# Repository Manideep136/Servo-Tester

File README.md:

# Servo-Tester
# Servo Tester

A simple standalone circuit for testing hobby servo motors by generating an adjustable PWM signal, without needing a microcontroller.
https://github.com/Manideep136/Servo-Tester/blob/main/sero%20tester/SERVO/TOP.png

## Overview

This circuit generates a variable-width PWM pulse (typically ~50Hz, 1ms–2ms pulse width) to drive a standard hobby servo, letting you manually sweep it or center it using a potentiometer — useful for testing, calibrating, or centering servos before installing them in a project.

## Circuit Description

*(Adjust the table below to match your actual component values)*

| Component | Value | Function |
|---|---|---|
| U1 | NE555 / LM555 | Astable/monostable oscillator generating the PWM signal |
| R1 | ~10kΩ (fixed) | Timing resistor |
| RV1 | 10kΩ Potentiometer | Adjusts pulse width (servo position) |
| C1 | ~10nF–100nF | Timing capacitor (sets base pulse frequency) |
| C2 | 10µF | Power supply decoupling capacitor |
| J1 | 3-pin header (Signal, VCC, GND) | Servo output connector |
| J2 | Screw Terminal / DC Jack | Power input (typically 4.8V–6V) |

## Schematic

https://github.com/Manideep136/Servo-Tester/blob/main/sero%20tester/SERVO/schematic.png

## PCB Layout

https://github.com/Manideep136/Servo-Tester/blob/main/sero%20tester/SERVO/LAYOUT.png

## Files

- `*.kicad_pro`, `*.kicad_sch`, `*.kicad_pcb` — KiCad project, schematic, and PCB layout files
- `gerbers/` — Fabrication files (Gerber + drill files) ready to send to a PCB manufacturer
- `images/` — Renders and screenshots of the schematic, PCB, and 3D model

## How to Use

1. Open `Servo-Tester.kicad_pro` in KiCad to view or edit the schematic and PCB.
2. To manufacture the board, send the contents of `gerbers/` to your preferred PCB fab (e.g. JLCPCB, PCBWay).
3. Connect a servo to the 3-pin output header (matching Signal/VCC/GND orientation to your servo's connector).
4. Power the board with 4.8V–6V DC.
5. Turn the potentiometer to sweep the servo from one end to the other, or center it to find the servo's neutral position.

## Notes

- Double-check your servo's signal pin orientation before connecting — reversed polarity can damage the servo or the tester.
- If using a 555 timer in astable mode, verify your R/C values produce a ~50Hz signal with a 1ms–2ms high pulse range (standard servo PWM range) using an oscilloscope or logic analyzer if available.
- A small heatsink or careful current limiting isn't usually necessary for a single small servo, but avoid powering multiple/large servos directly from this board without a beefier supply.

## License

Feel free to specify a license here (e.g. MIT, CERN-OHL) if you'd like others to reuse this design.

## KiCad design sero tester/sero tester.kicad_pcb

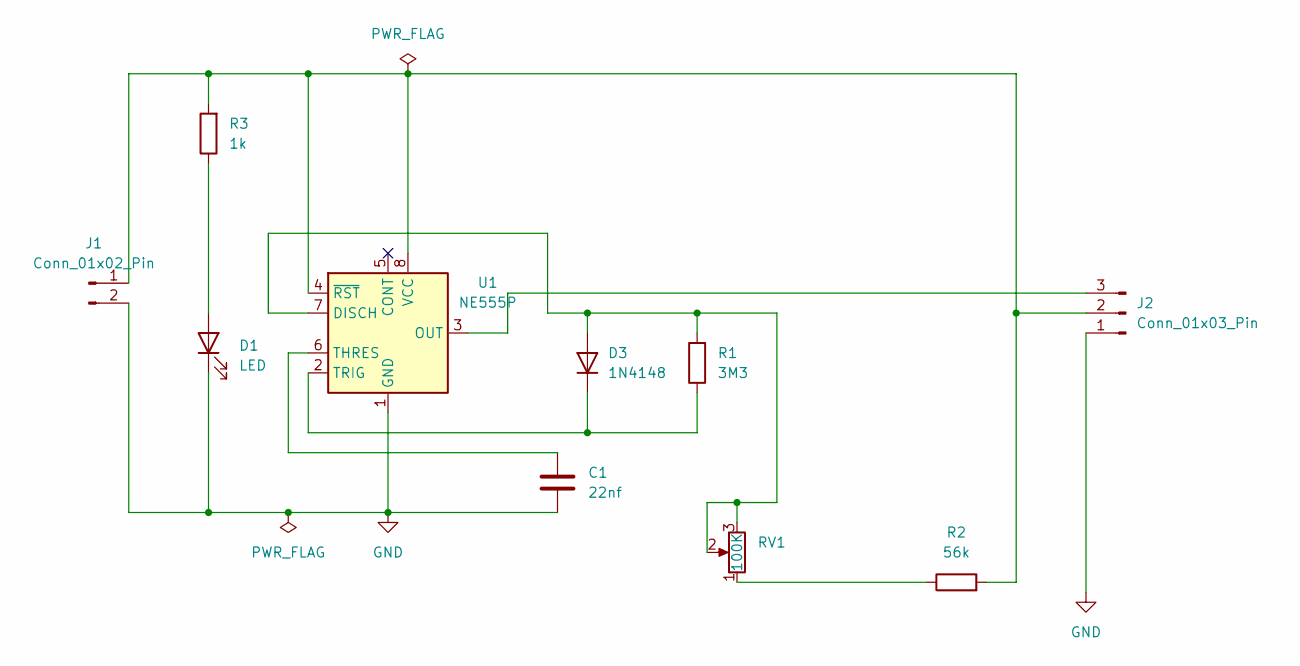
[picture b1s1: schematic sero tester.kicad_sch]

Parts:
C1: 22nf; C_Disc_D4.3mm_W1.9mm_P5.00mm
D1: LED; LED_D3.0mm
D3: 1N4148; D_DO-35_SOD27_P7.62mm_Horizontal
J1: Conn_01x02_Pin; PinHeader_1x02_P2.54mm_Horizontal
J2: Conn_01x03_Pin; PinHeader_1x03_P2.54mm_Horizontal
R1: 3M3; R_Axial_DIN0207_L6.3mm_D2.5mm_P7.62mm_Horizontal
R2: 56k; R_Axial_DIN0207_L6.3mm_D2.5mm_P7.62mm_Horizontal
R3: 1k; R_Axial_DIN0207_L6.3mm_D2.5mm_P7.62mm_Horizontal
RV1: 100K; Potentiometer_Alps_RK09K_Single_Horizontal
U1: NE555P; DIP-8_W7.62mm

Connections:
GND: C1.2, D1.1 (K), J1.2, J2.1, U1.1 (GND)
unnamed: D1.2 (A), R3.1
unnamed: D3.2 (A), R1.2, RV1.2, RV1.3, U1.7 (DISCH)
unnamed: D3.1 (K), R1.1, U1.2 (TRIG)
unnamed: J1.1, J2.2, R2.2, R3.2, U1.4 (~RST), U1.8 (VCC)
unnamed: J2.3, U1.3 (OUT)
unnamed: R2.1, RV1.1
unnamed: C1.1, U1.6 (THRES)

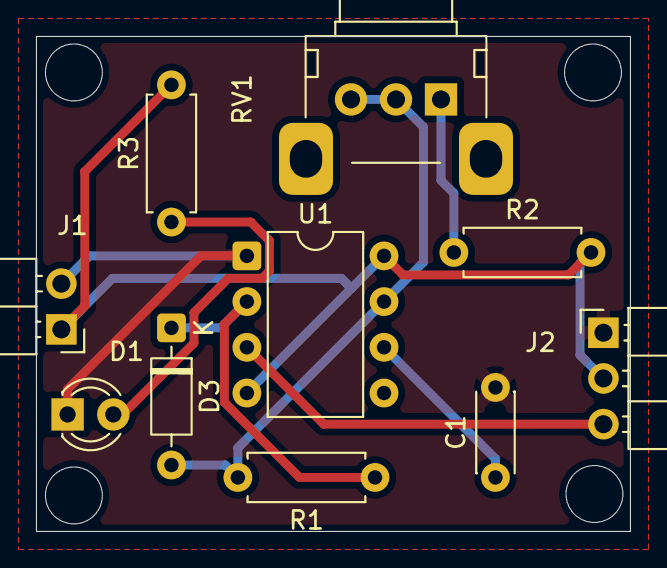
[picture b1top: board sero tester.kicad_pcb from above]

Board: 2 copper layers, 33.0 x 27.5 mm, 10 parts (0 on the bottom side), 8 nets.
